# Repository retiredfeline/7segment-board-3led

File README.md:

# 7 segment 2 digit board with 3 LEDs per segment

These are the design files for a 7 segment board for [Ancient 12 hour display](https://hackaday.io/project/184942-ancient-12-hour-display) but which can be used with modern 5mm LEDs.

## Versioning

Release March 2025

## Notes

Most components are installed on the back side and the LEDs are installed on the front side.

The board is designed to be cascadable by using the versatile 74HC595 shift register which only requires 3 lines to drive, plus power. Two boards stiched together with jumpers form 4 digits. You can see there is room for lots of driver transistors and base resistors. Those are only needed for these old LEDs due to their inefficiency and higher current draw. Modern LEDs with current draw 6 mA or less can be driven directly from the 74HC595 using the solder jumpers to bypass the transistors. The LED current limiting resistor is a resistor network which reduces component count but discrete resistors can be used instead if preferred. Remember that VDC - 3 x LED voltage drop should not exceed VCC.

## Authors

* **Ken Yap**

## License

See the [LICENSE](LICENSE.md) file for license rights and limitations (MIT).

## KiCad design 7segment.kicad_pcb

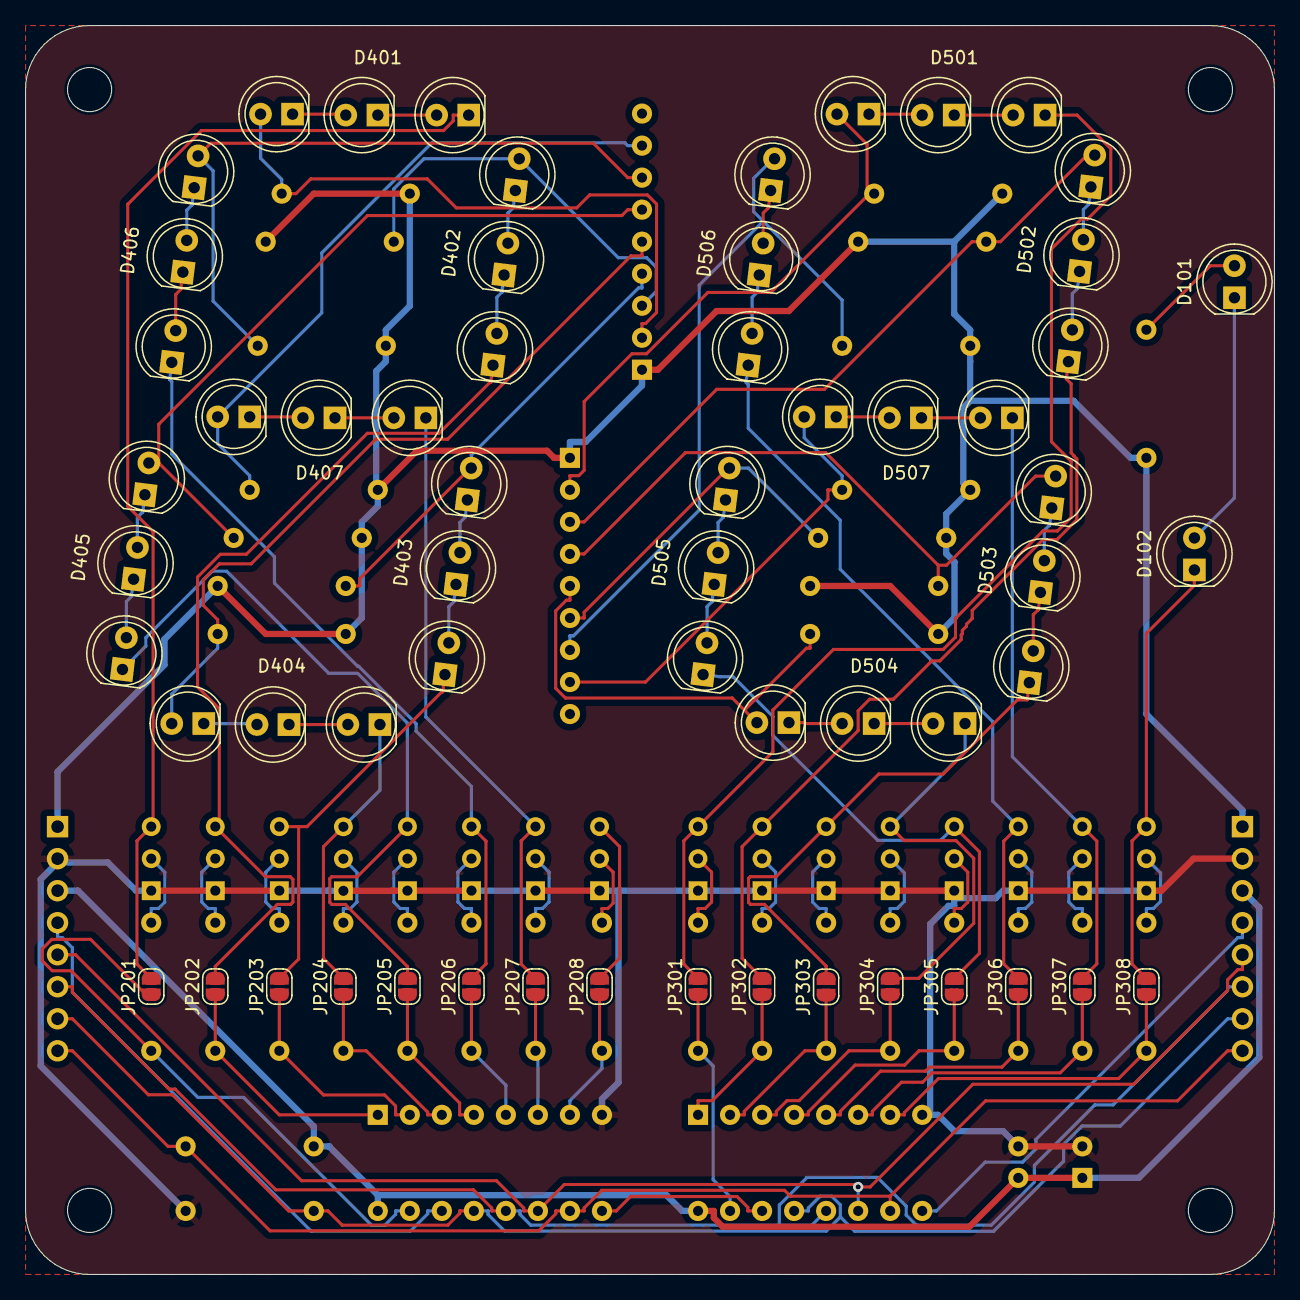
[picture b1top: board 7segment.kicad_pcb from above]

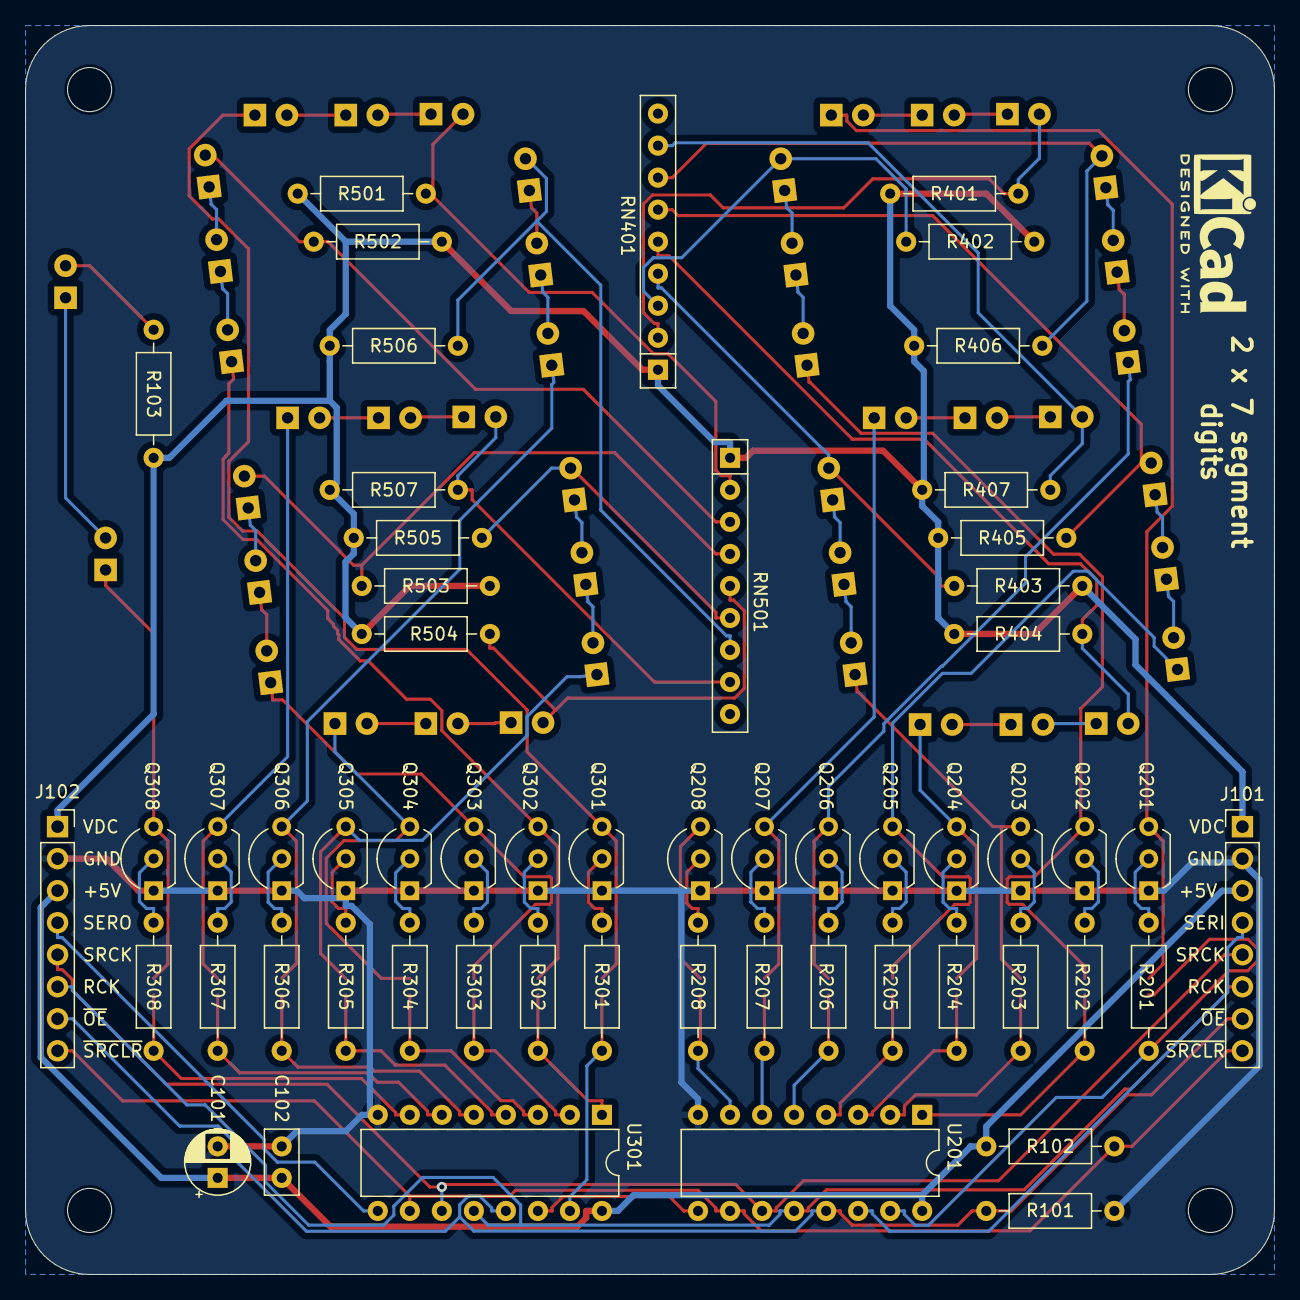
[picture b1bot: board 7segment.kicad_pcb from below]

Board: 2 copper layers, 99.1 x 99.1 mm, 93 parts (57 on the bottom side), 74 nets.

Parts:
C101: 10uF; CP_Radial_D5.0mm_P2.50mm
C102: 100nF; C_Disc_D5.0mm_W2.5mm_P2.50mm
D101, D102: Colon; LED_D5.0mm
D401, D501: A; LED_D5.0mmx3
D402, D502: B; LED_D5.0mmx3
D403, D503: C; LED_D5.0mmx3
D404, D504: D; LED_D5.0mmx3
D405, D505: E; LED_D5.0mmx3
D406, D506: F; LED_D5.0mmx3
D407, D507: G; LED_D5.0mmx3
H1, H2, H3, H4: MountingHole; MountingHole_3.5mm
J101: IN; PinHeader_1x08_P2.54mm_Vertical
J102: CHAIN; PinSocket_1x08_P2.54mm_Vertical
JP201, JP202, JP203, JP204, JP205, JP206, JP207, JP208, JP301, JP302, JP303, JP304, JP305, JP306, JP307, JP308: bypass; SolderJumper-2_P1.3mm_Open_RoundedPad1.0x1.5mm
Q201, Q301: A; TO-92L_Inline_Wide
Q202, Q302: B; TO-92L_Inline_Wide
Q203, Q303: C; TO-92L_Inline_Wide
Q204, Q304: D; TO-92L_Inline_Wide
Q205, Q305: E; TO-92L_Inline_Wide
Q206, Q306: F; TO-92L_Inline_Wide
Q207, Q307: G; TO-92L_Inline_Wide
Q208, Q308: P; TO-92L_Inline_Wide
R101, R102, R201, R202, R203, R204, R205, R206, R207, R208, R301, R302, R303, R304, R305, R306, R307, R308: 47k; R_Axial_DIN0207_L6.3mm_D2.5mm_P10.16mm_Horizontal
R103: 2k2; R_Axial_DIN0207_L6.3mm_D2.5mm_P10.16mm_Horizontal
R401, R402, R403, R404, R405, R406, R407, R501, R502, R503, R504, R505, R506, R507: 1k; R_Axial_DIN0207_L6.3mm_D2.5mm_P10.16mm_Horizontal
RN401, RN501: 1kx8; R_Array_SIP9
U201, U301: 74HC595; DIP-16_W7.62mm

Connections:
+5V: C101.1, C102.1, J101.3, J102.3, R102.2, U201.16 (VCC), U301.16 (VCC)
/Digit 1/A: D401.1 (K), JP201.2 (B), Q201.3 (C)
/Digit 1/AA: D401.2 (A), R401.2, RN401.2 (R1)
/Digit 1/AB: D402.2 (A), R402.2, RN401.3 (R2)
/Digit 1/AC: D403.2 (A), R403.2, RN401.4 (R3)
/Digit 1/AD: D404.2 (A), R404.2, RN401.5 (R4)
/Digit 1/AE: D405.2 (A), R405.1, RN401.6 (R5)
/Digit 1/AF: D406.2 (A), R406.1, RN401.7 (R6)
/Digit 1/AG: D407.2 (A), R407.2, RN401.8 (R7)
/Digit 1/B: D402.1 (K), JP202.2 (B), Q202.3 (C)
/Digit 1/C: D403.1 (K), JP203.2 (B), Q203.3 (C)
/Digit 1/D: D404.1 (K), JP204.2 (B), Q204.3 (C)
/Digit 1/E: D405.1 (K), JP205.2 (B), Q205.3 (C)
/Digit 1/F: D406.1 (K), JP206.2 (B), Q206.3 (C)
/Digit 1/G: D407.1 (K), JP207.2 (B), Q207.3 (C)
/Digit 2/A: D501.1 (K), JP301.2 (B), Q301.3 (C)
/Digit 2/AA: D501.2 (A), R501.2, RN501.2 (R1)
/Digit 2/AB: D502.2 (A), R502.2, RN501.3 (R2)
/Digit 2/AC: D503.2 (A), R503.2, RN501.4 (R3)
/Digit 2/AD: D504.2 (A), R504.2, RN501.5 (R4)
/Digit 2/AE: D505.2 (A), R505.1, RN501.6 (R5)
/Digit 2/AF: D506.2 (A), R506.1, RN501.7 (R6)
/Digit 2/AG: D507.2 (A), R507.2, RN501.8 (R7)
/Digit 2/B: D502.1 (K), JP302.2 (B), Q302.3 (C)
/Digit 2/C: D503.1 (K), JP303.2 (B), Q303.3 (C)
/Digit 2/D: D504.1 (K), JP304.2 (B), Q304.3 (C)
/Digit 2/E: D505.1 (K), JP305.2 (B), Q305.3 (C)
/Digit 2/F: D506.1 (K), JP306.2 (B), Q306.3 (C)
/Digit 2/G: D507.1 (K), JP307.2 (B), Q307.3 (C)
/SR driver 1/P: JP208.2 (B), Q208.3 (C)
/SR driver 1/QH: U201.9 (QH'), U301.14 (SER)
/SR driver 1/RCLK: J101.6, J102.6, U201.12 (RCLK), U301.12 (RCLK)
/SR driver 1/SER: J101.4, U201.14 (SER)
/SR driver 1/SRCLK: J101.5, J102.5, U201.11 (SRCLK), U301.11 (SRCLK)
/SR driver 1/~OE: J101.7, J102.7, R101.2, U201.13 (~OE), U301.13 (~OE)
/SR driver 1/~SRCLR: J101.8, J102.8, R102.1, U201.10 (~SRCLR), U301.10 (~SRCLR)
/SR driver 2/P: D102.1 (K), JP308.2 (B), Q308.3 (C)
/SR driver 2/QH: J102.4, U301.9 (QH')
GND: C101.2, C102.2, J101.2, J102.2, Q201.1 (E), Q202.1 (E), Q203.1 (E), Q204.1 (E), Q205.1 (E), Q206.1 (E), Q207.1 (E), Q208.1 (E), Q301.1 (E), Q302.1 (E), Q303.1 (E), Q304.1 (E), Q305.1 (E), Q306.1 (E), Q307.1 (E), Q308.1 (E), R101.1, U201.8 (GND), U301.8 (GND)
unnamed: D101.2 (A), R103.1
unnamed: D101.1 (K), D102.2 (A)
unnamed: JP201.1 (A), R201.1, U201.15 (QA)
unnamed: JP202.1 (A), R202.1, U201.1 (QB)
unnamed: JP203.1 (A), R203.1, U201.2 (QC)
unnamed: JP204.1 (A), R204.1, U201.3 (QD)
unnamed: JP205.1 (A), R205.1, U201.4 (QE)
unnamed: JP206.1 (A), R206.1, U201.5 (QF)
unnamed: JP207.1 (A), R207.1, U201.6 (QG)
unnamed: JP208.1 (A), R208.1, U201.7 (QH)
unnamed: JP301.1 (A), R301.1, U301.15 (QA)
unnamed: JP302.1 (A), R302.1, U301.1 (QB)
unnamed: JP303.1 (A), R303.1, U301.2 (QC)
unnamed: JP304.1 (A), R304.1, U301.3 (QD)
unnamed: JP305.1 (A), R305.1, U301.4 (QE)
unnamed: JP306.1 (A), R306.1, U301.5 (QF)
unnamed: JP307.1 (A), R307.1, U301.6 (QG)
unnamed: JP308.1 (A), R308.1, U301.7 (QH)
unnamed: Q201.2 (B), R201.2
unnamed: Q202.2 (B), R202.2
unnamed: Q203.2 (B), R203.2
unnamed: Q204.2 (B), R204.2
unnamed: Q205.2 (B), R205.2
unnamed: Q206.2 (B), R206.2
unnamed: Q207.2 (B), R207.2
unnamed: Q208.2 (B), R208.2
unnamed: Q301.2 (B), R301.2
unnamed: Q302.2 (B), R302.2
unnamed: Q303.2 (B), R303.2
unnamed: Q304.2 (B), R304.2
unnamed: Q305.2 (B), R305.2
unnamed: Q306.2 (B), R306.2
unnamed: Q307.2 (B), R307.2
unnamed: Q308.2 (B), R308.2
VDC: J101.1, J102.1, R103.2, R401.1, R402.1, R403.1, R404.1, R405.2, R406.2, R407.1, R501.1, R502.1, R503.1, R504.1, R505.2, R506.2, R507.1, RN401.1 (common), RN501.1 (common)

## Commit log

2024-03-20 First version
2025-03-12 Add gerbers
2025-03-12 Add README.md and LICENSE.md
2025-04-16 Use copyright symbol
